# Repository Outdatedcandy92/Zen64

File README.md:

# Zen64

Zen64 is a super minimal 64 key wireless mechanical keyboard with hot-swap sockets and a sliding potentiometer. It uses the nice!nano board as its controller and features a sleek modern design.

--- 

## Project Structure

```
Zen64/
├── BOM.md
├── JOURNAL.md
├── README.md
└── src/
    ├── cad/
    │   └── MinimalKeeb v5.step
    ├── firmware/
    │   └── code.py
    ├── kicad/
    │   ├── Keyboard.kicad_pcb
    │   ├── Keyboard.kicad_prl
    │   ├── Keyboard.kicad_pro
    │   └── Keyboard.kicad_sch
    └── production/
        ├── Bottom_Feet_10deg.stl
        ├── Case.stl
        ├── Keyboard_Plate.stl
        ├── Keyboard.zip
        └── Potentiometer_Cover.stl

```

### Schematics

### PCB

### PCB Render

### Fusion 360

## BOM

| Componenet                                                                                                                                                                                                                                                                                                                                                                                                                                                                                                                                                                                                                                   | Quantity | Price           |
| -------------------------------------------------------------------------------------------------------------------------------------------------------------------------------------------------------------------------------------------------------------------------------------------------------------------------------------------------------------------------------------------------------------------------------------------------------------------------------------------------------------------------------------------------------------------------------------------------------------------------------------------- | -------- | --------------- |
| [Kalih Hot Swap Socket](https://www.aliexpress.com/item/1005008954571807.html?spm=a2g0o.productlist.main.2.55feMl65Ml65s2&algo_pvid=f8397f2a-7bf2-49ac-bbab-e2d704af1f0e&algo_exp_id=f8397f2a-7bf2-49ac-bbab-e2d704af1f0e-1&pdp_ext_f=%7B%22order%22%3A%2255%22%2C%22eval%22%3A%221%22%7D&pdp_npi=4%40dis%21CAD%2111.22%215.61%21%21%2157.62%2128.81%21%402101e07217514235212394334eaffe%2112000047352129246%21sea%21CA%216156843420%21X&curPageLogUid=Q4Fb00KaI6zO&utparam-url=scene%3Asearch%7Cquery_from%3A)                                                                                                                              | 70pcs    | 11.18           |
| [Cherry MX Red](https://www.aliexpress.com/item/1005006255961111.html?spm=a2g0o.productlist.main.1.25072154vwYIt1&algo_pvid=c2aec9e9-30b8-4903-86ec-93dc45616b59&algo_exp_id=c2aec9e9-30b8-4903-86ec-93dc45616b59-0&pdp_ext_f=%7B%22order%22%3A%221051%22%2C%22eval%22%3A%221%22%7D&pdp_npi=4%40dis%21CAD%218.94%218.41%21%21%2145.94%2143.24%21%402101c5b117514236040725960ef9f9%2112000036489552472%21sea%21CA%216156843420%21X&curPageLogUid=0N9jVLK4P2WV&utparam-url=scene%3Asearch%7Cquery_from%3A)                                                                                                                                     | 70pcs    | 28.18           |
| [Keycap Set](https://www.aliexpress.com/item/1005006431348409.html?spm=a2g0o.productlist.main.6.7009sK9csK9c7s&algo_pvid=0c3ab69b-1c0c-4e45-993c-63d37fc5c20d&algo_exp_id=0c3ab69b-1c0c-4e45-993c-63d37fc5c20d-5&pdp_ext_f=%7B%22order%22%3A%22815%22%2C%22eval%22%3A%221%22%7D&pdp_npi=4%40dis%21CAD%2130.06%2128.53%21%21%2121.58%2120.48%21%402101e9ec17514237059447899e8627%2112000037143457598%21sea%21CA%216156843420%21X&curPageLogUid=ztjQVqGxNto8&utparam-url=scene%3Asearch%7Cquery_from%3A)                                                                                                                                       | 1 set    | 28.84           |
| [Stabilizer Set](https://www.aliexpress.com/item/1005007041109896.html?spm=a2g0o.productlist.main.17.2b9724e6VcNj9Q&algo_pvid=82175921-c7da-4a01-b7bf-391bce48a28c&algo_exp_id=82175921-c7da-4a01-b7bf-391bce48a28c-14&pdp_ext_f=%7B%22order%22%3A%229%22%2C%22eval%22%3A%221%22%7D&pdp_npi=4%40dis%21CAD%218.59%218.59%21%21%216.17%216.17%21%402101c59517514238829131534e7f20%2112000039190570197%21sea%21CA%216156843420%21X&curPageLogUid=WQRecSvLlIHL&utparam-url=scene%3Asearch%7Cquery_from%3A#nav-specification)                                                                                                                     | 1 set    | 8.59            |
| [Nice!Nano Clone](https://www.aliexpress.com/item/1005007205026373.html?spm=a2g0o.productlist.main.4.4df46d47SX33K7&aem_p4p_detail=2025070119430812586835491530040001108866&algo_pvid=fb83c095-23c2-4a8d-a869-7bc7d247f5cb&algo_exp_id=fb83c095-23c2-4a8d-a869-7bc7d247f5cb-3&pdp_ext_f=%7B%22order%22%3A%22304%22%2C%22eval%22%3A%221%22%7D&pdp_npi=4%40dis%21CAD%215.46%215.21%21%21%2128.06%2126.76%21%402101e9ec17514241884904612e862f%2112000039797470328%21sea%21CA%216156843420%21X&curPageLogUid=AuVvUd8DmT8c&utparam-url=scene%3Asearch%7Cquery_from%3A&search_p4p_id=2025070119430812586835491530040001108866_1#nav-specification) | 2pcs     | 10.42           |
| [M2.5 6mm Heat Insert](https://www.aliexpress.com/item/1005003582355741.html?spm=a2g0o.cart.0.0.20ef38datcOXA1&mp=1&pdp_npi=5%40dis%21CAD%21CAD%203.36%21CAD%203.03%21%21CAD%203.03%21%21%21%402101c80017514246487655933eb539%2112000026370649786%21ct%21CA%216156843420%21%211%210&pdp_ext_f=%7B%22cart2PdpParams%22%3A%7B%22pdpBusinessMode%22%3A%22retail%22%7D%7D)                                                                                                                                                                                                                                                                       | 30pcs    | 2.92            |
| [M2.5 8mm Screws](https://www.aliexpress.com/item/32810852732.html?spm=a2g0o.productlist.main.1.49a410dde4PUtG&algo_pvid=b11e6406-bf21-4606-9862-09dca0e01f30&algo_exp_id=b11e6406-bf21-4606-9862-09dca0e01f30-0&pdp_ext_f=%7B%22order%22%3A%2213876%22%2C%22eval%22%3A%221%22%7D&pdp_npi=4%40dis%21CAD%212.90%212.80%21%21%212.08%212.01%21%40210330dd17514248211287729e133c%2112000037550700724%21sea%21CA%216156843420%21X&curPageLogUid=LbYhNB23J6Ey&utparam-url=scene%3Asearch%7Cquery_from%3A)                                                                                                                                         | 50pcs    | 2.34            |
| [MCP23017-SO](https://www.aliexpress.com/item/1005005066054098.html?spm=a2g0o.productlist.main.2.4c8f1bfen3fKs1&algo_pvid=e98fa7ce-2684-42a1-ba07-1fadf12c1554&algo_exp_id=e98fa7ce-2684-42a1-ba07-1fadf12c1554-1&pdp_ext_f=%7B%22order%22%3A%2293%22%2C%22eval%22%3A%221%22%7D&pdp_npi=4%40dis%21CAD%218.72%218.72%21%21%216.26%216.26%21%402101c5bf17514248865652806ed473%2112000031503785206%21sea%21CA%216156843420%21X&curPageLogUid=V8HojXL7bwvY&utparam-url=scene%3Asearch%7Cquery_from%3A)                                                                                                                                           | 5pcs     | 8.72            |
| [1N4148 SOD-123](https://www.aliexpress.com/item/1005005574663623.html?spm=a2g0o.productlist.main.2.47a77ef0SHcwvI&algo_pvid=525b4ada-6b92-4b53-a8c7-2fc9b97ea9e9&algo_exp_id=525b4ada-6b92-4b53-a8c7-2fc9b97ea9e9-1&pdp_ext_f=%7B%22order%22%3A%2219%22%2C%22eval%22%3A%221%22%7D&pdp_npi=4%40dis%21CAD%212.81%212.81%21%21%2114.41%2114.41%21%402103244b17514249984487326e0630%2112000033607802195%21sea%21CA%216156843420%21X&curPageLogUid=vivYB1FRD5du&utparam-url=scene%3Asearch%7Cquery_from%3A)                                                                                                                                      | 100pcs   | 2.99            |
| [10K Slide Potentiometer](https://www.aliexpress.com/item/32988914044.html?spm=a2g0o.productlist.main.28.7859pCMgpCMgKT&algo_pvid=e9c64538-3178-405d-b31c-bbe5bfd21724&algo_exp_id=e9c64538-3178-405d-b31c-bbe5bfd21724-25&pdp_ext_f=%7B%22order%22%3A%2236%22%2C%22eval%22%3A%221%22%7D&pdp_npi=4%40dis%21CAD%2112.92%2111.89%21%21%219.22%218.48%21%402101c80017513185600476508eb51b%2166909972400%21sea%21CA%216156843420%21X&curPageLogUid=QxJoA1Z0F6IA&utparam-url=scene%3Asearch%7Cquery_from%3A#nav-specification)                                                                                                                    | 10pcs    | 11.18           |
| [Non Slip Feet](https://www.aliexpress.com/item/1005007555926154.html?spm=a2g0o.productlist.main.5.2913502at9TYLB&algo_pvid=06730e04-126b-4299-af95-1b35347b83d5&algo_exp_id=06730e04-126b-4299-af95-1b35347b83d5-4&pdp_ext_f=%7B%22order%22%3A%2216%22%2C%22eval%22%3A%221%22%7D&pdp_npi=4%40dis%21CAD%214.19%214.19%21%21%213.01%213.01%21%402101e07217514251229264789eafff%2112000041278493817%21sea%21CA%216156843420%21X&curPageLogUid=UaIqALG0mDkz&utparam-url=scene%3Asearch%7Cquery_from%3A)                                                                                                                                         | 1pc      | 4.19            |
| [EVA Foam 3mm](https://www.aliexpress.com/item/1005005567697486.html?spm=a2g0o.productlist.main.1.53465a64yNQTSQ&algo_pvid=9f92ae23-c53d-49a9-b2d3-de4b8f0cd4f8&algo_exp_id=9f92ae23-c53d-49a9-b2d3-de4b8f0cd4f8-0&pdp_ext_f=%7B%22order%22%3A%223861%22%2C%22eval%22%3A%221%22%7D&pdp_npi=4%40dis%21CAD%216.62%215.93%21%21%2134.00%2130.46%21%402101ef5e17514251642997534ea7f4%2112000033581949723%21sea%21CA%216156843420%21X&curPageLogUid=v9yykN5XmOcs&utparam-url=scene%3Asearch%7Cquery_from%3A)                                                                                                                                      | 1pc      | 5.99            |
| PCB                                                                                                                                                                                                                                                                                                                                                                                                                                                                                                                                                                                                                                          | 5pcs     | 27.22           |
| [PETG Filament](https://www.amazon.ca/gp/product/B0D41Y3WWZ?smid=A2WWHQ25ENKVJ1&th=1)                                                                                                                                                                                                                                                                                                                                                                                                                                                                                                                                                        | 1kg      | 28.61           |
| [USB-C Cable](https://www.aliexpress.com/item/1005007512342949.html?spm=a2g0o.productlist.main.3.36c5760aiJanzj&algo_pvid=d62827ba-c92d-4e13-8d12-368e807dce9b&algo_exp_id=d62827ba-c92d-4e13-8d12-368e807dce9b-2&pdp_ext_f=%7B%22order%22%3A%224106%22%2C%22eval%22%3A%221%22%7D&pdp_npi=4%40dis%21CAD%219.73%219.18%21%21%216.97%216.58%21%402101ead817514262858736205ea2ad%2112000041081409457%21sea%21CA%216156843420%21X&curPageLogUid=64XhL0QAJ8UV&utparam-url=scene%3Asearch%7Cquery_from%3A)                                                                                                                                         | 1pc      | 9.08            |
| [Solder Wire](https://www.aliexpress.com/item/1005007053733373.html?spm=a2g0o.productlist.main.1.4bf850dfTHAAOa&algo_pvid=5c2a71f5-1125-4102-a0df-05d98aa4430e&algo_exp_id=5c2a71f5-1125-4102-a0df-05d98aa4430e-0&pdp_ext_f=%7B%22order%22%3A%2210184%22%2C%22eval%22%3A%221%22%7D&pdp_npi=4%40dis%21CAD%215.69%215.34%21%21%2129.18%2127.38%21%402103244617514313613333277ef76a%2112000046556938711%21sea%21CA%216156843420%21X&curPageLogUid=rbQiTdx2BLmT&utparam-url=scene%3Asearch%7Cquery_from%3A#nav-specification)                                                                                                                    | 50G      | 8.83            |
| [2mm Silicon Foam](https://www.aliexpress.com/item/1005006922115651.html?spm=a2g0o.productlist.main.1.3a5b13edq9SjcB&algo_pvid=81febd34-f56c-4203-b1cc-b69634393ffc&algo_exp_id=81febd34-f56c-4203-b1cc-b69634393ffc-0&pdp_ext_f=%7B%22order%22%3A%22560%22%2C%22eval%22%3A%221%22%7D&pdp_npi=4%40dis%21CAD%216.73%216.73%21%21%214.82%214.82%21%40210318ec17511375801223275ea690%2112000039495180613%21sea%21CA%216156843420%21X&curPageLogUid=aeBTp4O1X7D4&utparam-url=scene%3Asearch%7Cquery_from%3A#nav-specification)                                                                                                                   | 1pc      | 9.99            |
| Subtotal                                                                                                                                                                                                                                                                                                                                                                                                                                                                                                                                                                                                                                     |          | $209.27 CAD     |
| Discount                                                                                                                                                                                                                                                                                                                                                                                                                                                                                                                                                                                                                                     |          | -$16            |
| Total                                                                                                                                                                                                                                                                                                                                                                                                                                                                                                                                                                                                                                        |          | $193 = $142 USD |

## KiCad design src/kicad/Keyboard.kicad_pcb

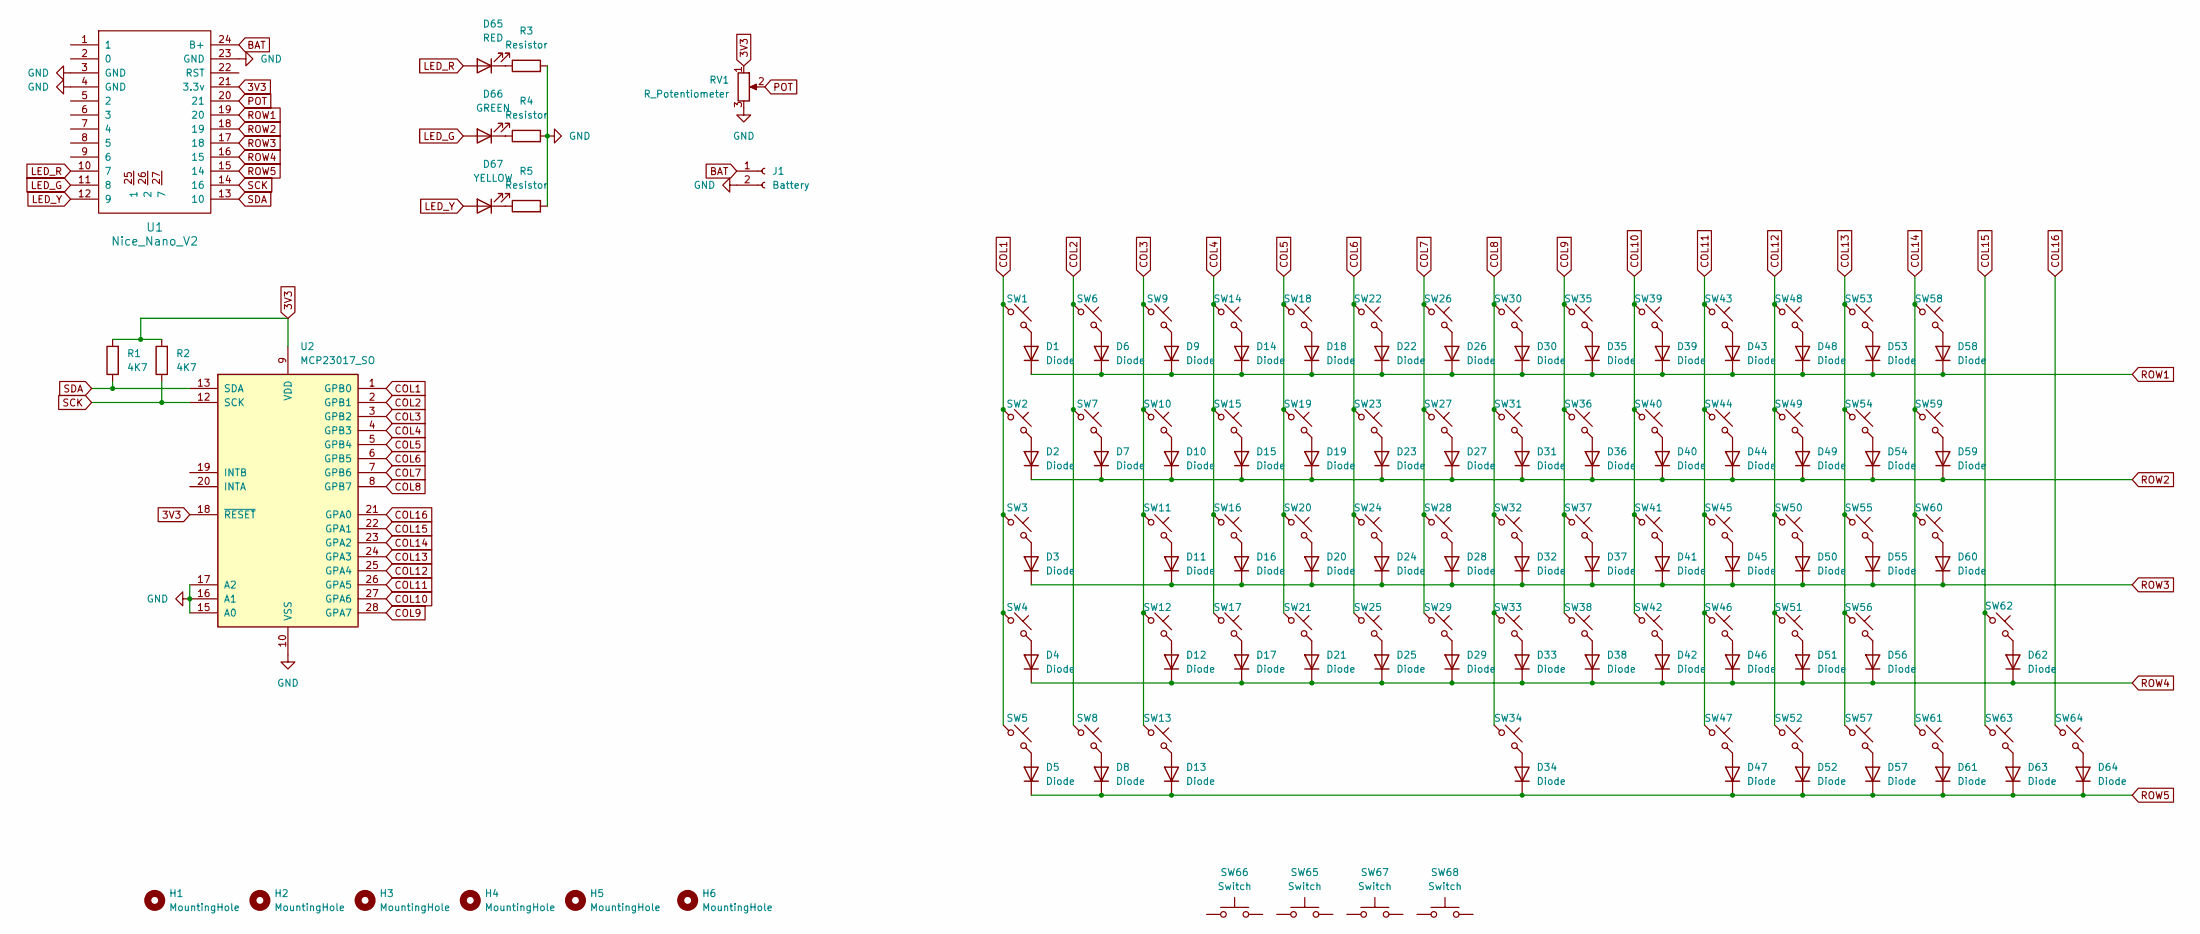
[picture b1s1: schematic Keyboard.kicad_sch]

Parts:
D1, D2, D3, D4, D5, D6, D7, D8, D9, D10, D11, D12, D13, D14, D15, D16, D17, D18, D19, D20, D21, D22, D23, D24, D25, D26, D27, D28, D29, D30, D31, D32, D33, D34, D35, D36, D37, D38, D39, D40, D41, D42, D43, D44, D45, D46, D47, D48, D49, D50, D51, D52, D53, D54, D55, D56, D57, D58, D59, D60, D61, D62, D63, D64: Diode; D_0805_2012Metric_Pad1.15x1.40mm_HandSolder
D65: RED; LED_0805_2012Metric_Pad1.15x1.40mm_HandSolder
D66: GREEN; LED_0805_2012Metric_Pad1.15x1.40mm_HandSolder
D67: YELLOW; LED_0805_2012Metric_Pad1.15x1.40mm_HandSolder
H1, H2, H3, H4, H5, H6: MountingHole; MountingHole_2.7mm_M2.5
J1: Battery; JST_XH_B2B-XH-AM_1x02_P2.50mm_Vertical
R1, R2: 4K7; R_0805_2012Metric_Pad1.20x1.40mm_HandSolder
R3, R4, R5: Resistor; R_0805_2012Metric_Pad1.20x1.40mm_HandSolder
RV1: R_Potentiometer; Sliding_Pot
SW1, SW6, SW7, SW8, SW9, SW10, SW11, SW12, SW13, SW14, SW15, SW16, SW17, SW18, SW19, SW20, SW21, SW22, SW23, SW24, SW25, SW26, SW27, SW28, SW29, SW30, SW31, SW32, SW33, SW35, SW36, SW37, SW38, SW39, SW40, SW41, SW42, SW43, SW44, SW45, SW46, SW48, SW49, SW50, SW51, SW53, SW54, SW55, SW57, SW61, SW62, SW63, SW64: SW_Push_45deg; Hotswap_MX_Plated_1.00u
SW2, SW59: SW_Push_45deg; Hotswap_MX_Plated_1.50u
SW3, SW56: SW_Push_45deg; Hotswap_MX_Plated_1.75u
SW4, SW60: SW_Push_45deg; Hotswap_MX_Plated_2.25u
SW5, SW47, SW52: SW_Push_45deg; Hotswap_MX_Plated_1.25u
SW34: SW_Push_45deg; Hotswap_MX_Plated_6.25u
SW58: SW_Push_45deg; Hotswap_MX_Plated_2.00u
SW65, SW66, SW67: Switch; Stabilizer_MX_2.00u
SW68: Switch; Stabilizer_MX_6.25u
U1: Nice_Nano_V2
U2: MCP23017_SO; SOIC-28W_7.5x17.9mm_P1.27mm

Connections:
3V3: R1.2, R2.2, RV1.1, U1.21 (3.3v), U2.9 (VDD), U2.18 (~RESET)
BAT: J1.1, U1.24 (B+)
COL1: SW1.1, SW2.1, SW3.1, SW4.1, SW5.1, U2.1 (GPB0)
COL2: SW6.1, SW7.1, SW8.1, U2.2 (GPB1)
COL3: SW9.1, SW10.1, SW11.1, SW12.1, SW13.1, U2.3 (GPB2)
COL4: SW14.1, SW15.1, SW16.1, SW17.1, U2.4 (GPB3)
COL5: SW18.1, SW19.1, SW20.1, SW21.1, U2.5 (GPB4)
COL6: SW22.1, SW23.1, SW24.1, SW25.1, U2.6 (GPB5)
COL7: SW26.1, SW27.1, SW28.1, SW29.1, U2.7 (GPB6)
COL8: SW30.1, SW31.1, SW32.1, SW33.1, SW34.1, U2.8 (GPB7)
COL9: SW35.1, SW36.1, SW37.1, SW38.1, U2.28 (GPA7)
COL10: SW39.1, SW40.1, SW41.1, SW42.1, U2.27 (GPA6)
COL11: SW43.1, SW44.1, SW45.1, SW46.1, SW47.1, U2.26 (GPA5)
COL12: SW48.1, SW49.1, SW50.1, SW51.1, SW52.1, U2.25 (GPA4)
COL13: SW53.1, SW54.1, SW55.1, SW56.1, SW57.1, U2.24 (GPA3)
COL14: SW58.1, SW59.1, SW60.1, SW61.1, U2.23 (GPA2)
COL15: SW62.1, SW63.1, U2.22 (GPA1)
COL16: SW64.1, U2.21 (GPA0)
GND: J1.2, R3.2, R4.2, R5.2, RV1.3, U1.3 (GND), U1.4 (GND), U1.23 (GND), U2.10 (VSS), U2.15 (A0), U2.16 (A1), U2.17 (A2)
LED_G: D66.2 (A), U1.11 (8)
LED_R: D65.2 (A), U1.10 (7)
LED_Y: D67.2 (A), U1.12 (9)
unnamed: D1.2 (A), SW1.2
unnamed: D2.2 (A), SW2.2
unnamed: D3.2 (A), SW3.2
unnamed: D4.2 (A), SW4.2
unnamed: D5.2 (A), SW5.2
unnamed: D6.2 (A), SW6.2
unnamed: D7.2 (A), SW7.2
unnamed: D8.2 (A), SW8.2
unnamed: D9.2 (A), SW9.2
unnamed: D10.2 (A), SW10.2
unnamed: D11.2 (A), SW11.2
unnamed: D12.2 (A), SW12.2
unnamed: D13.2 (A), SW13.2
unnamed: D14.2 (A), SW14.2
unnamed: D15.2 (A), SW15.2
unnamed: D16.2 (A), SW16.2
unnamed: D17.2 (A), SW17.2
unnamed: D18.2 (A), SW18.2
unnamed: D19.2 (A), SW19.2
unnamed: D20.2 (A), SW20.2
unnamed: D21.2 (A), SW21.2
unnamed: D22.2 (A), SW22.2
unnamed: D23.2 (A), SW23.2
unnamed: D24.2 (A), SW24.2
unnamed: D25.2 (A), SW25.2
unnamed: D26.2 (A), SW26.2
unnamed: D27.2 (A), SW27.2
unnamed: D28.2 (A), SW28.2
unnamed: D29.2 (A), SW29.2
unnamed: D30.2 (A), SW30.2
unnamed: D31.2 (A), SW31.2
unnamed: D32.2 (A), SW32.2
unnamed: D33.2 (A), SW33.2
unnamed: D34.2 (A), SW34.2
unnamed: D35.2 (A), SW35.2
unnamed: D36.2 (A), SW36.2
unnamed: D37.2 (A), SW37.2
unnamed: D38.2 (A), SW38.2
unnamed: D39.2 (A), SW39.2
unnamed: D40.2 (A), SW40.2
unnamed: D41.2 (A), SW41.2
unnamed: D42.2 (A), SW42.2
unnamed: D43.2 (A), SW43.2
unnamed: D44.2 (A), SW44.2
unnamed: D45.2 (A), SW45.2
unnamed: D46.2 (A), SW46.2
unnamed: D47.2 (A), SW47.2
unnamed: D48.2 (A), SW48.2
unnamed: D49.2 (A), SW49.2
unnamed: D50.2 (A), SW50.2
unnamed: D51.2 (A), SW51.2
unnamed: D52.2 (A), SW52.2
unnamed: D53.2 (A), SW53.2
unnamed: D54.2 (A), SW54.2
unnamed: D55.2 (A), SW55.2
unnamed: D56.2 (A), SW56.2
unnamed: D57.2 (A), SW57.2
unnamed: D58.2 (A), SW58.2
unnamed: D59.2 (A), SW59.2
unnamed: D60.2 (A), SW60.2
unnamed: D61.2 (A), SW61.2
unnamed: D62.2 (A), SW62.2
unnamed: D63.2 (A), SW63.2
unnamed: D64.2 (A), SW64.2
unnamed: D65.1 (K), R3.1
unnamed: D66.1 (K), R4.1
unnamed: D67.1 (K), R5.1
POT: RV1.2, U1.20 (21)
ROW1: D1.1 (K), D6.1 (K), D9.1 (K), D14.1 (K), D18.1 (K), D22.1 (K), D26.1 (K), D30.1 (K), D35.1 (K), D39.1 (K), D43.1 (K), D48.1 (K), D53.1 (K), D58.1 (K), U1.19 (20)
ROW2: D2.1 (K), D7.1 (K), D10.1 (K), D15.1 (K), D19.1 (K), D23.1 (K), D27.1 (K), D31.1 (K), D36.1 (K), D40.1 (K), D44.1 (K), D49.1 (K), D54.1 (K), D59.1 (K), U1.18 (19)
ROW3: D3.1 (K), D11.1 (K), D16.1 (K), D20.1 (K), D24.1 (K), D28.1 (K), D32.1 (K), D37.1 (K), D41.1 (K), D45.1 (K), D50.1 (K), D55.1 (K), D60.1 (K), U1.17 (18)
ROW4: D4.1 (K), D12.1 (K), D17.1 (K), D21.1 (K), D25.1 (K), D29.1 (K), D33.1 (K), D38.1 (K), D42.1 (K), D46.1 (K), D51.1 (K), D56.1 (K), D62.1 (K), U1.16 (15)
ROW5: D5.1 (K), D8.1 (K), D13.1 (K), D34.1 (K), D47.1 (K), D52.1 (K), D57.1 (K), D61.1 (K), D63.1 (K), D64.1 (K), U1.15 (14)
SCK: R2.1, U1.14 (16), U2.12 (SCK)
SDA: R1.1, U1.13 (10), U2.13 (SDA)

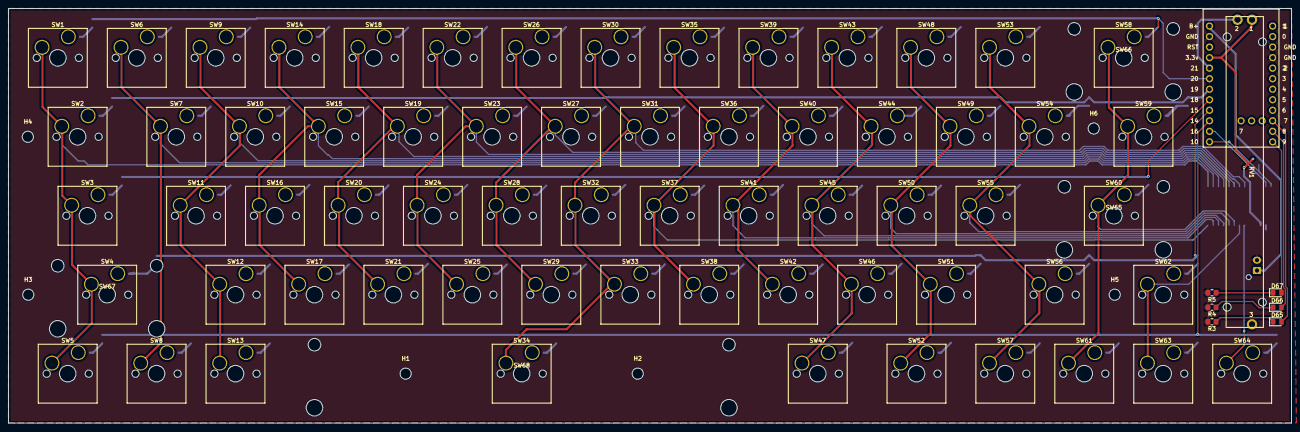
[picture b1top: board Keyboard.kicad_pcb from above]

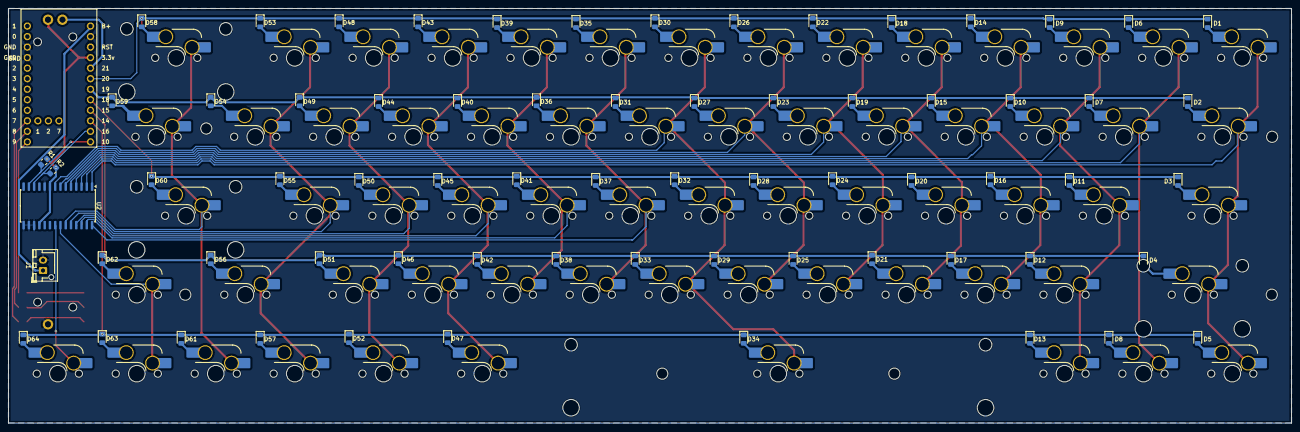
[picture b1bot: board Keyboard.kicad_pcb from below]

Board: 2 copper layers, 309.6 x 100.0 mm, 150 parts (69 on the bottom side), 97 nets.

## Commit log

2025-07-03 firmware
